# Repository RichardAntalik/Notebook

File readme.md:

# RPI CM5 based notebook

The design of small notebook with 8 inch display.
This is mainly a fun project, excersise in device production capability and integration
of complex systems at my home lab.

At revision 3 most subsystems are tested and working, but not as a whole.

## Features
- Smol
- 2 layer PCB layout! Optimized for home production
- Has integrated power management for 1S lipo pack
- Implements 4xUSB + 2 internal ports, 1x HDMI + 1 internal HDMI and DSI/CSI, PCIe, GPIO in card format and simple sound output

## TODO
- Custom keyboard with some touchpad or trackball or whatnot
- Display board
- Case

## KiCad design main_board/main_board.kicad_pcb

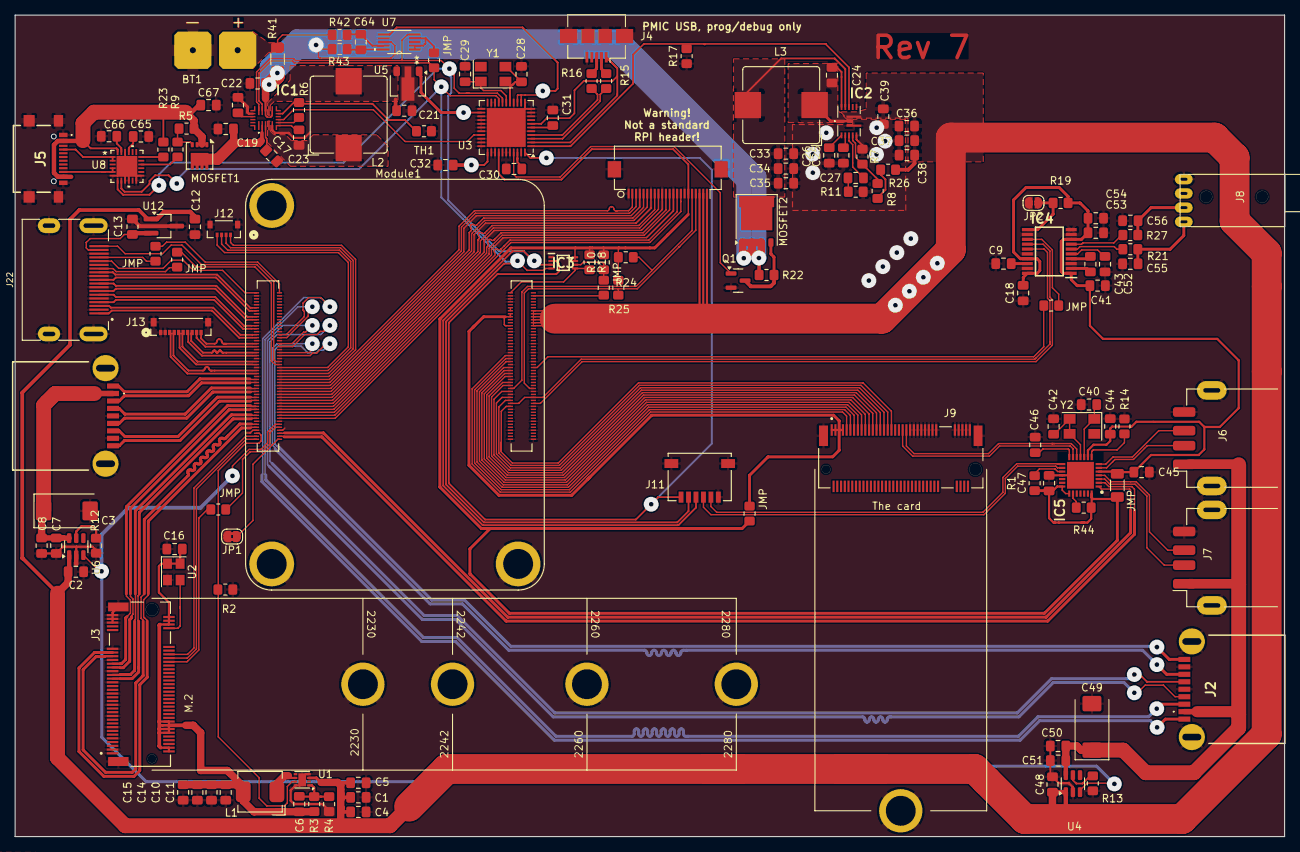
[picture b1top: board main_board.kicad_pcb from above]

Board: 2 copper layers, 170.0 x 110.0 mm, 139 parts (0 on the bottom side), 161 nets.

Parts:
BT1: Battery_Cell; Bat_terminal
C1, C2, C4, C7, C8, C10, C11, C14, C15, C17, C20, C21, C22, C26, C48, C50, C51, C54: 10u; C_0805_2012Metric_Pad1.18x1.45mm_HandSolder
C3, C49: 100uF; CP_EIA-7343-31_Kemet-D
C5, C9, C12, C13, C16, C18, C24, C25, C39, C41, C44, C45, C46, C47, C53, C64: 100n; C_0805_2012Metric_Pad1.18x1.45mm_HandSolder
C6: 10nF; C_0805_2012Metric_Pad1.18x1.45mm_HandSolder
C19, C30, C31, C32, C65, C66, C67: 1u; C_0805_2012Metric_Pad1.18x1.45mm_HandSolder
C23, C27: 10n; C_0805_2012Metric_Pad1.18x1.45mm_HandSolder
C28, C29, C40, C42: 22p; C_0805_2012Metric_Pad1.18x1.45mm_HandSolder
C33, C34, C35, C36, C37, C38: 22u; C_0805_2012Metric_Pad1.18x1.45mm_HandSolder
C43, C52: 2u2; C_0805_2012Metric_Pad1.18x1.45mm_HandSolder
C55, C56: 2n2; C_0805_2012Metric_Pad1.18x1.45mm_HandSolder
IC1: MP2722GRH-0000-Z; MP2722GRH0000Z
IC2: MP3429GL-Z; MP3431GLP
IC3: PCA9306DCUR; SOP50P310X90-8N
IC4: PCM5102APWR; SOP65P640X120-20N
IC5: CY7C65632-28LTXC; QFN50P500X500X80-29N-D
J1, J2: USB3_A; U3BU1ASMT1
J3: Bus_M.2_Socket_M; M.2 M Key socket
J4: USB_B_Micro; USB_Micro-B_Amphenol_10104110_Horizontal
J5: USB_C_Receptacle_USB2.0; USB421603A
J6, J7: USB_A; USB_A_Receptacle_GCT_USB1046
J8: AudioJack3; LUMBERG 1503 16
J9: The_card; Random card conn
J10: Conn_01x22_Female; Hirose_FH12-22S-0.5SH_1x22-1MP_P0.50mm_Horizontal
J11: 501568-0607-TR325; CONN_501568-0607-TR325_MOL
J12: SM04B-XSRS-ETBLFSN; CONN_SM04B-XSRS-ETB_JST
J13: SM10B-XSRS-ETB; CONN_SM10B-XSRS-ETB_JST
J22: 690-019-298-412; EDAC 690-019-298-412
JMP: R_0805_2012Metric_Pad1.20x1.40mm_HandSolder
JMP#2, JMP#3, JMP#5, JMP#6, JMP#7, JMP#8: R_0805_2012Metric_Pad1.20x1.40mm_HandSolder
JMP#4: 0.01R; R_1206_3216Metric_Pad1.30x1.75mm_HandSolder
JP1: Jumper_2_Bridged; SolderJumper-2_P1.3mm_Bridged2Bar_RoundedPad1.0x1.5mm
JP2: Jumper_2; SolderJumper-2_P1.3mm_Open_RoundedPad1.0x1.5mm
L1: 2.2uH; L_Bourns_SRP5030CC
L2: 4.7u; L_Bourns_SRP1038C_10.0x10.0mm
L3: 1.5u; L_Bourns_SRP1038C_10.0x10.0mm
MOSFET1: STL9P3LLH6; Diodes_PowerDI3333-8
MOSFET2: WMB60P02TS-CYG; PQFN-8-EP_6x5mm_P1.27mm_Generic
Module1: ComputeModule5-CM5; Raspberry-Pi-5-Compute-Module
Q1: Random N ch FET; SOT-23
R1, R9: 10K; R_0805_2012Metric_Pad1.20x1.40mm_HandSolder
R2: 100K 1%; R_0805_2012Metric_Pad1.20x1.40mm_HandSolder
R3, R17: 15K; R_0805_2012Metric_Pad1.20x1.40mm_HandSolder
R4: 3.3K; R_0805_2012Metric_Pad1.20x1.40mm_HandSolder
R5, R7, R19, R22: 100K; R_0805_2012Metric_Pad1.20x1.40mm_HandSolder
R6: R=NTC; R_0805_2012Metric_Pad1.20x1.40mm_HandSolder
R8: 68K; R_0805_2012Metric_Pad1.20x1.40mm_HandSolder
R10, R18, R24, R25: 2K; R_0805_2012Metric_Pad1.20x1.40mm_HandSolder
R11: 6.8K; R_0805_2012Metric_Pad1.20x1.40mm_HandSolder
R12, R13: 15K 1%; R_0805_2012Metric_Pad1.20x1.40mm_HandSolder
R14: 650R; R_0805_2012Metric_Pad1.20x1.40mm_HandSolder
R15, R16: 20R; R_0805_2012Metric_Pad1.20x1.40mm_HandSolder
R21, R27: 470R; R_0805_2012Metric_Pad1.20x1.40mm_HandSolder
R23: 1K; R_0805_2012Metric_Pad1.20x1.40mm_HandSolder
R26: 330K; R_0805_2012Metric_Pad1.20x1.40mm_HandSolder
R41: 0.01R; R_1206_3216Metric_Pad1.30x1.75mm_HandSolder
R42, R43: 10R; R_0805_2012Metric_Pad1.20x1.40mm_HandSolder
R44: 100k; R_0805_2012Metric_Pad1.20x1.40mm_HandSolder
TH1: β = 3435; R_0805_2012Metric_Pad1.20x1.40mm_HandSolder
U1: AP3441SHE-7B; DFN-8-1EP_2x2mm_P0.5mm_EP1.05x1.75mm
U2: ASEK-32.768KHZ-L-R-T; Crystal_SMD_3225-4Pin_3.2x2.5mm
U3: ATmega32U4-M; QFN-44-1EP_7x7mm_P0.5mm_EP5.2x5.2mm
U4, U6: AP22653W6; SOT-23-6
U5: AP2204RB-3.3; SOT-89-3
U7: INA220AIDGST; DGS10
U8: STUSB4500QTR; STUSB4500
U12: RT9742SNGV; TSOT-23_HandSoldering
Y1: Crystal; Crystal_SMD_5032-4Pin_5.0x3.2mm
Y2: 12MHz; Crystal_SMD_5032-4Pin_5.0x3.2mm

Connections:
/Battery management/+5V: C1.1, C2.1, C4.1, C5.1, C12.1, C36.1, C37.1, C38.1, C39.1, C48.1, IC2.8 (VOUT), J10.20, J10.21, J10.22, Module1.77 (+5v_(Input)), Module1.79 (+5v_(Input)), Module1.81 (+5v_(Input)), Module1.83 (+5v_(Input)), Module1.85 (+5v_(Input)), Module1.87 (+5v_(Input)), R26.2, U1.3 (VIN), U4.1 (IN), U6.1 (IN), U12.1 (IN)
/Battery management/BOOST_EN: IC2.11 (EN), R17.2, U3.1 (PE6)
/Battery management/PMIC_3.3V: C32.2, IC3.2 (VREF1), J11.6, U3.13 (~RESET), U3.14 (VCC), U3.24 (AVCC), U3.34 (VCC), U3.44 (AVCC), U5.1 (VOUT), U7.6 (VS)
/Battery management/PMIC_IIC2_SCL: IC3.6 (SCL2), JMP#7.1, JMP#7.2, Module1.97 (CAM_GPIO0), R10.1
/Battery management/PMIC_IIC2_SDA: IC3.5 (SDA2), Module1.100 (CAM_GPIO1), R18.2
/Battery management/PMIC_IIC_SCL: IC1.16 (SCL), IC3.3 (SCL1), J11.4, U3.18 (PD0), U7.5 (SCL), U8.7 (SCL)
/Battery management/PMIC_IIC_SDA: IC1.15 (SDA), IC3.4 (SDA1), J11.5, JMP#3.1, U3.19 (PD1), U7.1 (A1), U7.2 (A0), U7.4 (SDA), U8.8 (SDA)
/Battery management/VBAT: C22.1, IC1.12 (BATTSNS), IC1.14 (BATT), MOSFET2.1 (S), MOSFET2.2 (S), MOSFET2.3 (S), R22.2, R41.2, R43.2, U7.8 (VBUS)
/Battery management/V_SYS: C21.1, IC1.13 (SYS), L2.2, U5.3 (VIN)
/CM5_GPIO/+1.8v: Module1.88 (+1.8v_(Output)), Module1.90 (+1.8v_(Output))
/CM5_GPIO/+3.3v: C18.1, C41.2, C44.1, C45.1, C47.1, C53.2, C54.2, IC3.7 (VREF2), IC3.8 (EN), IC4.1 (CPVDD), IC4.8 (AVDD), IC4.17 (XSMT), IC4.20 (DVDD), IC5.5 (VCC_A_1), IC5.9 (VCC_A_2), IC5.21 (VCC_D), IC5.22 (SELFPWR), IC5.28 (VREG), J9.1, J9.3, J9.5, J9.7, J10.17, JMP#4.1, JMP#4.2, JMP#5.1, JMP#5.2, Module1.78 (GPIO_VREF(1.8v/3.3v_Input)), Module1.84 (+3.3v_(Output)), Module1.86 (+3.3v_(Output)), R1.1, R10.2, R18.1, R19.2, R24.1, R25.1, R44.1, U3.37 (PF6)
/CM5_GPIO/DPHY1_SCL: J10.19, Module1.35 (ID_SC), R25.2
/CM5_GPIO/DPHY1_SDA: J10.18, Module1.36 (ID_SD), R24.2
/CM5_GPIO/GP2: J9.9, Module1.58 (GPIO2)
/CM5_GPIO/GP3: J9.11, Module1.56 (GPIO3)
/CM5_GPIO/GP4: J9.13, Module1.54 (GPIO4)
/CM5_GPIO/GP5: J9.27, Module1.34 (GPIO5)
/CM5_GPIO/GP6: J9.29, Module1.30 (GPIO6)
/CM5_GPIO/GP9: J9.23, Module1.40 (GPIO9)
/CM5_GPIO/GP10: J9.21, Module1.44 (GPIO10)
/CM5_GPIO/GP11: J9.25, Module1.38 (GPIO11)
/CM5_GPIO/GP13: J9.31, Module1.28 (GPIO13)
/CM5_GPIO/GP17: J9.15, Module1.50 (GPIO17)
/CM5_GPIO/GP22: J9.19, Module1.46 (GPIO22)
/CM5_GPIO/GP26: J9.33, Module1.24 (GPIO26)
/CM5_GPIO/GP27: J9.17, Module1.48 (GPIO27)
/CM5_GPIO/GPIO16: IC4.15 (LRCK), Module1.26 (GPIO19), Module1.29 (GPIO16)
/CM5_GPIO/I2SCLK: IC4.13 (BCK), JMP#6.1, JMP#6.2, Module1.49 (GPIO18)
/CM5_HighSpeed/DPHY0_C_N: J10.9, Module1.127 (MIPI0_C_N)
/CM5_HighSpeed/DPHY0_C_P: J10.8, Module1.129 (MIPI0_C_P)
/CM5_HighSpeed/DPHY0_D0_N: J10.15, Module1.115 (MIPI0_D0_N)
/CM5_HighSpeed/DPHY0_D0_P: J10.14, Module1.117 (MIPI0_D0_P)
/CM5_HighSpeed/DPHY0_D1_N: J10.12, Module1.121 (MIPI0_D1_N)
/CM5_HighSpeed/DPHY0_D1_P: J10.11, Module1.123 (MIPI0_D1_P)
/CM5_HighSpeed/DPHY0_D2_N: J10.6, Module1.133 (MIPI0_D2_N)
/CM5_HighSpeed/DPHY0_D2_P: J10.5, Module1.135 (MIPI0_D2_P)
/CM5_HighSpeed/DPHY0_D3_N: J10.3, Module1.139 (MIPI0_D3_N)
/CM5_HighSpeed/DPHY0_D3_P: J10.2, Module1.141 (MIPI0_D3_P)
/CM5_HighSpeed/HDMI0_CEC: J22.13 (CEC), JMP#2.1, JMP#2.2, Module1.151 (HDMI0_CEC)
/CM5_HighSpeed/HDMI0_CK_N: J22.12 (CK-), Module1.190 (HDMI0_CLK_N)
/CM5_HighSpeed/HDMI0_CK_P: J22.10 (CK+), Module1.188 (HDMI0_CLK_P)
/CM5_HighSpeed/HDMI0_D0_N: J22.9 (D0-), Module1.184 (HDMI0_TX0_N)
/CM5_HighSpeed/HDMI0_D0_P: J22.7 (D0+), Module1.182 (HDMI0_TX0_P)
/CM5_HighSpeed/HDMI0_D1_N: J22.6 (D1-), Module1.178 (HDMI0_TX1_N)
/CM5_HighSpeed/HDMI0_D1_P: J22.4 (D1+), Module1.176 (HDMI0_TX1_P)
/CM5_HighSpeed/HDMI0_D2_N: J22.3 (D2-), Module1.172 (HDMI0_TX2_N)
/CM5_HighSpeed/HDMI0_D2_P: J22.1 (D2+), Module1.170 (HDMI0_TX2_P)
/CM5_HighSpeed/HDMI0_HOTPLUG: J22.19 (HPD/HEAC-), Module1.153 (HDMI0_HOTPLUG)
/CM5_HighSpeed/HDMI0_SCL: J22.15 (SCL), Module1.200 (HDMI0_SCL)
/CM5_HighSpeed/HDMI0_SDA: J22.16 (SDA), JMP#8.1, JMP#8.2, Module1.199 (HDMI0_SDA)
/CM5_HighSpeed/HDMI1_CEC: J12.4, Module1.149 (HDMI1_CEC)
/CM5_HighSpeed/HDMI1_CK_N: J13.10, Module1.166 (HDMI1_CLK_N)
/CM5_HighSpeed/HDMI1_CK_P: J13.9, Module1.164 (HDMI1_CLK_P)
/CM5_HighSpeed/HDMI1_D0_N: J13.8, Module1.160 (HDMI1_TX0_N)
/CM5_HighSpeed/HDMI1_D0_P: J13.7, Module1.158 (HDMI1_TX0_P)
/CM5_HighSpeed/HDMI1_D1_N: J13.6, Module1.154 (HDMI1_TX1_N)
/CM5_HighSpeed/HDMI1_D1_P: J13.5, Module1.152 (HDMI1_TX1_P)
/CM5_HighSpeed/HDMI1_D2_N: J13.4, Module1.148 (HDMI1_TX2_N)
/CM5_HighSpeed/HDMI1_D2_P: J13.3, Module1.146 (HDMI1_TX2_P)
/CM5_HighSpeed/HDMI1_HOTPLUG: J12.1, Module1.143 (HDMI1_HOTPLUG)
/CM5_HighSpeed/HDMI1_SCL: J12.3, Module1.147 (HDMI1_SCL)
/CM5_HighSpeed/HDMI1_SDA: J12.2, Module1.145 (HDMI1_SDA)
/CM5_HighSpeed/HDMI_5v: C13.1, J22.18 (+5V), U12.2 (OUT)
/CM5_HighSpeed/PCIE_CLK_N: J3.53 (REFCLKn), Module1.112 (PCIe_CLK_N)
/CM5_HighSpeed/PCIE_CLK_P: J3.55 (REFCLKp), Module1.110 (PCIe_CLK_P)
/CM5_HighSpeed/PCIE_PWR_EN: Module1.106 (PCIE_PWR_EN), R2.1, U1.7 (EN)
/CM5_HighSpeed/PCIE_RX_N: J3.43 (PETp0), Module1.118 (PCIe_RX_N)
/CM5_HighSpeed/PCIE_RX_P: J3.41 (PETn0), Module1.116 (PCIe_RX_P)
/CM5_HighSpeed/PCIE_TX_N: J3.49 (PERp0), Module1.124 (PCIe_TX_N)
/CM5_HighSpeed/PCIE_TX_P: J3.47 (PERn0), Module1.122 (PCIe_TX_P)
/CM5_HighSpeed/PCIE_nCLKREQ: J3.52 (~CLKREQ), Module1.102 (PCIe_nCLKREQ)
/CM5_HighSpeed/PCIE_nRST: J3.50 (~PERST), JMP.1, JMP.2, Module1.109 (PCIe_nRST)
/CM5_HighSpeed/PCIE_nWAKE: J3.54 (~PEWAKE), Module1.104 (PCIE_nWAKE)
/CM5_HighSpeed/USB2_N: IC5.1 (D-), Module1.105 (USB2_P)
/CM5_HighSpeed/USB2_P: IC5.2 (D+), Module1.103 (USB2_N)
/CM5_HighSpeed/USB3-0-D_N: J1.2 (D-), Module1.136 (USB3-0-D_N)
/CM5_HighSpeed/USB3-0-D_P: J1.3 (D+), Module1.134 (USB3-0-D_P)
/CM5_HighSpeed/USB3-0-RX_N: J1.5 (SSRX-), Module1.128 (USB3-0-RX_N)
/CM5_HighSpeed/USB3-0-RX_P: J1.6 (SSRX+), Module1.130 (USB3-0-RX_P)
/CM5_HighSpeed/USB3-0-TX_N: J1.8 (SSTX-), Module1.140 (USB3-0-TX_N)
/CM5_HighSpeed/USB3-0-TX_P: J1.9 (SSTX+), Module1.142 (USB3-0-TX_P)
/CM5_HighSpeed/VBUS: C3.1, C7.1, C8.1, J1.1 (VBUS), U6.6 (OUT)
/CM5_HighSpeed/VBUS_EN: Module1.111 (VBUS_EN), U4.3 (EN), U6.3 (EN)
/PCIe-M2/FB: C6.2, R3.2, R4.1, U1.1 (FB)
/PCIe-M2/M2_3v3: C6.1, C10.1, C11.1, C14.1, C15.1, C16.1, J3.2 (3.3V), J3.4 (3.3V), J3.12 (3.3V), J3.14 (3.3V), J3.16 (3.3V), J3.18 (3.3V), J3.70 (3.3V), J3.72 (3.3V), J3.74 (3.3V), L1.2, R3.1, U2.1 (EN), U2.4 (VDD)
/The card/USB2_2_DN: IC5.12 (DD-[3]), J9.41
/The card/USB2_2_DP: IC5.13 (DD+[3]), J9.39
/USB hub/VBUS2: C49.1, C50.1, C51.1, J2.1 (VBUS), J6.1 (VBUS), J7.1 (VBUS), U4.6 (OUT)
GND: BT1.2 (-), C1.2, C2.2, C3.2, C4.2, C5.2, C7.2, C8.2, C9.2, C10.2, C11.2, C12.2, C13.2, C14.2, C15.2, C16.2, C17.2, C18.2, C19.2, C20.2, C21.2, C22.2, C25.1, C26.1, C28.2, C29.2, C30.1, C31.1, C32.1, C33.2, C34.2, C35.2, C36.2, C37.2, C38.2, C39.2, C40.2, C41.1, C42.2, C44.2, C45.2, C46.2, C47.2, C48.2, C49.2, C50.2, C51.2, C52.1, C53.1, C54.1, C55.1, C56.1, C65.2, C66.2, C67.2, IC1.5 (PGND), IC1.18 (AGND), IC2.6 (AGND), IC2.7 (PGND), IC2.9 (FTY), IC3.1 (GND), IC4.3 (CPGND), IC4.9 (AGND), IC4.10 (DEMP), IC4.12 (SCK), IC4.16 (FMT), IC4.19 (DGND), IC5.18 (TEST/_I2C_SCL), IC5.29 (EP), J1.4 (GND), J1.7 (DRAIN), J1.10 (SHIELD), J2.4 (GND), J2.7 (DRAIN), J2.10 (SHIELD), J3.1 (GND), J3.3 (GND), J3.9 (GND), J3.15 (GND), J3.21 (GND), J3.27 (GND), J3.33 (GND), J3.39 (GND), J3.45 (GND), J3.51 (GND), J3.57 (GND), J3.71 (GND), J3.73 (GND), J3.75 (GND), J3.M1 (GND2230), J3.M2 (GND2242), J3.M3 (GND2260), J3.M4 (GND2280), J3.S1, J3.S2, J4.5 (GND), J4.6 (Shield), J5.A1 (GND), J5.B1 (GND), J5.S1 (SHIELD), J6.4 (GND), J6.5 (Shield), J7.4 (GND), J7.5 (Shield), J8.S, J9.43, J9.45, J9.47, J9.49, J9.51, J9.53, J9.55, J9.57, J9.67, J9.69, J9.71, J9.73, J9.75, J9.M1 (GND2230), J9.S1, J9.S2, J10.1, J10.4, J10.7, J10.10, J10.13, J10.16, J10.MP, J11.1, J11.7, J11.8, J12.5, J12.6, J13.1, J13.2, J13.11, J13.12, J22.2 (D2S), J22.5 (D1S), J22.8 (D0S), J22.11 (CKS), J22.17 (GND), J22.SH1 (SH), J22.SH2 (SH), J22.SH3 (SH), J22.SH4 (SH), JP1.2 (B), JP2.2 (B), Module1.1 (GND), Module1.2 (GND), Module1.7 (GND), Module1.8 (GND), Module1.13 (GND), Module1.14 (GND), Module1.22 (GND), Module1.23 (GND), Module1.32 (GND), Module1.33 (GND), Module1.42 (GND), Module1.43 (GND), Module1.52 (GND), Module1.53 (GND), Module1.59 (GND), Module1.60 (GND), Module1.65 (GND), Module1.66 (GND), Module1.71 (GND), Module1.74 (GND), Module1.94 (CC1), Module1.96 (CC2), Module1.98 (GND), Module1.107 (GND), Module1.108 (GND), Module1.113 (GND), Module1.114 (GND), Module1.119 (GND), Module1.120 (GND), Module1.125 (GND), Module1.126 (GND), Module1.131 (GND), Module1.132 (GND), Module1.137 (GND), Module1.138 (GND), Module1.144 (GND), Module1.150 (GND), Module1.155 (GND), Module1.156 (GND), Module1.161 (GND), Module1.162 (GND), Module1.167 (GND), Module1.168 (GND), Module1.173 (GND), Module1.174 (GND), Module1.179 (GND), Module1.180 (GND), Module1.185 (GND), Module1.186 (GND), Module1.191 (GND), Module1.192 (GND), Module1.197 (GND), Module1.198 (GND), Module1.MP, Q1.2 (S), R2.2, R4.2, R7.1, R11.1, R12.1, R13.2, R14.2, R17.1, TH1.2, U1.4 (PGND), U1.8 (SGND), U1.9 (PAD), U2.2 (GND), U3.5 (UGND), U3.9 (PB1), U3.10 (PB2), U3.11 (PB3), U3.12 (PB7), U3.15 (GND), U3.20 (PD2), U3.21 (PD3), U3.23 (GND), U3.25 (PD4), U3.26 (PD6), U3.27 (PD7), U3.28 (PB4), U3.29 (PB5), U3.31 (PC6), U3.32 (PC7), U3.33 (~HWB/PE2), U3.35 (GND), U3.36 (PF7), U3.38 (PF5), U3.39 (PF4), U3.40 (PF1), U3.43 (GND), U3.45 (GND), U4.2 (GND), U5.2 (GND), U6.2 (GND), U7.7 (GND), U8.6 (RESET), U8.9 (DISCH), U8.10 (GND), U8.12 (ADDR0), U8.13 (ADDR1), U8.22 (VSYS), U8.25 (EP), U12.3 (GND)
unnamed: BT1.1 (+), R41.1, R42.2
unnamed: C27.1, R11.2
unnamed: C55.2, J8.T, R21.1
unnamed: C56.2, J8.R1, R27.1
unnamed: C23.2, IC1.6 (BST_1)
unnamed: C19.1, IC1.2 (IN), MOSFET1.5 (D)
unnamed: IC1.10 (NTC1), R6.1, TH1.1
unnamed: C17.1, IC1.3 (PMID)
unnamed: C23.1, IC1.4 (SW), L2.1
unnamed: C20.1, IC1.19 (VCC)
unnamed: IC1.7 (VRNTC), R6.2
unnamed: IC1.8 (~INT), U3.30 (PB6)
unnamed: C24.1, IC2.13 (BST)
unnamed: C27.2, IC2.4 (COMP)
unnamed: IC2.5 (FB), R7.2, R8.1
unnamed: C25.2, IC2.3 (SS)
unnamed: C24.2, IC2.1 (SW), L3.1
unnamed: C26.2, IC2.2 (VDD)
unnamed: C33.1, C34.1, C35.1, IC2.12 (VIN), L3.2, MOSFET2.5 (D)
unnamed: C43.1, IC4.4 (CAPM)
unnamed: C43.2, IC4.2 (CAPP)
unnamed: IC4.14 (DIN), Module1.25 (GPIO21)
unnamed: IC4.11 (FLT), JP2.1 (A), R19.1
unnamed: C9.1, IC4.18 (LDOO)
unnamed: IC4.6 (OUTL), R21.2
unnamed: IC4.7 (OUTR), R27.2
unnamed: C52.2, IC4.5 (VNEG)
unnamed: IC5.4 (DD+[1]), J7.3 (D+)
unnamed: IC5.7 (DD+[2]), J6.3 (D+)
unnamed: IC5.16 (DD+[4]), J11.3
unnamed: IC5.3 (DD-[1]), J7.2 (D-)
unnamed: IC5.6 (DD-[2]), J6.2 (D-)
unnamed: IC5.15 (DD-[4]), J11.2
unnamed: IC5.23 (GANG), R44.2
unnamed: IC5.17 (RESET#), R1.2
unnamed: IC5.8 (RREF), R14.1
unnamed: C46.1, IC5.14 (VCC_A_3)
unnamed: C40.1, IC5.10 (XIN), Y2.1
unnamed: C42.1, IC5.11 (XOUT), Y2.2
unnamed: J2.3 (D+), Module1.163 (USB3-1-D_P)
unnamed: J2.2 (D-), Module1.165 (USB3-1-D_N)
unnamed: J2.6 (SSRX+), Module1.157 (USB3-1-RX_N)
unnamed: J2.5 (SSRX-), Module1.159 (USB3-1-RX_P)
unnamed: J2.9 (SSTX+), Module1.171 (USB3-1-TX_P)
unnamed: J2.8 (SSTX-), Module1.169 (USB3-1-TX_N)
unnamed: J3.68 (SUSCLK), U2.3 (Out)
unnamed: J4.3 (D+), R16.2
unnamed: J4.2 (D-), R15.2
unnamed: J4.1 (VBUS), U3.2 (UVCC), U3.7 (VBUS)
unnamed: J5.A5 (CC1), U8.1 (CC1DB), U8.2 (CC1)
unnamed: J5.B5 (CC2), U8.4 (CC2), U8.5 (CC2DB)
unnamed: JP1.1 (A), Module1.101 (USB_OTG_ID)
unnamed: MOSFET1.4 (G), R5.2, R9.1
unnamed: MOSFET2.4 (G), Q1.3 (D), R22.1
unnamed: Q1.1 (G), U3.41 (PF0)
unnamed: R8.2, R26.1
unnamed: L1.1, U1.6 (LX)
unnamed: C30.2, U3.42 (AREF)
unnamed: R16.1, U3.4 (D+)
unnamed: R15.1, U3.3 (D-)
unnamed: C31.2, U3.6 (UCAP)
unnamed: C29.1, U3.17 (XTAL1), Y1.1
unnamed: C28.1, U3.16 (XTAL2), Y1.2
unnamed: R13.1, U4.5 (ILIM)
unnamed: R12.2, U6.5 (ILIM)
unnamed: C64.2, R43.1, U7.10 (VIN+)
unnamed: C64.1, R42.1, U7.9 (VIN-)
unnamed: R9.2, U8.16 (VBUS_EN_SNK)
unnamed: R23.2, U8.18 (VBUS_VS_DISCH)
unnamed: C67.1, J5.A4 (VBUS), J5.B4 (VBUS), MOSFET1.1 (S), MOSFET1.2 (S), MOSFET1.3 (S), R5.1, R23.1, U8.24 (VDD)
unnamed: C65.1, U8.21 (VREG_1V2)
unnamed: C66.1, U8.23 (VREG_2V7)

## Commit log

2025-06-30 Add main board project
2025-06-30 Implement part of power management.
2025-07-01 More power management goodness
2025-07-02 Finalize power management
2025-07-03 Start reouting USB hub
2025-07-06 Bunch more routing, mainly added MIPI interface, reworked power management a bit
2025-07-12 Bunch of fixes + audio out interface
2025-07-12 Implement power monitoring
2025-07-13 Add expansion slot
2025-07-27 Rev 1 draft
2025-07-27 Cleanup silks
2025-07-28 Final fixes
2025-07-28 Also update schematic
2025-07-29 Fix fried USB hub
2025-07-30 Fix frying usb hub again
2025-07-30 Remove passives from hub
2025-07-30 Cleanup, improve ground situation
2025-07-30 More ground improvements
2025-08-04 Fix 32u4 high power consumption, improve QFN soldering with thick ass solder masks.
2025-08-05 Make sure, that audio jack can be hand soldered, finalize rev 1 design.
2025-08-05 Fix bad jack footprint
2025-08-05 Make all holes only 0.8mm for spot drilling only
2025-08-05 Add battery polarity labels to cu layer, since mistake would be expensive
2025-08-05 Change the board size, rev2
2025-08-07 Revert all holes defaulting to 0.8mm as plotter can do this
2025-08-07 Add mounting points to symbols
2025-08-07 Make more space for the card
2025-08-07 Change mech holes to TH for better hand spot drilling
2025-08-07 Silk cleanup
2025-08-07 Update readme and whatnot
2025-08-07 Update readme.md
    That's what I get for editing markup without preview...
2025-08-10 Rev 4
    Fix some mistakes found during assembly
2025-08-10 Fix bad output voltage
    For some reason I got 5V with previous values on prototype. Weird...
2025-08-12 Fix critical problems
    - Adding USB2 hub on USB3 port did not work correctly
    - PM I2C bus was not working when CM5 is shut down
    - Missing OTG ID pin
2025-08-13 Fix CM5 not waking up when enabling boost
    When battery is fully charged, CM5 does not turn on.
2025-08-15 Use I2S sound chip instead of PWM output
2025-08-16 Minor fixes
